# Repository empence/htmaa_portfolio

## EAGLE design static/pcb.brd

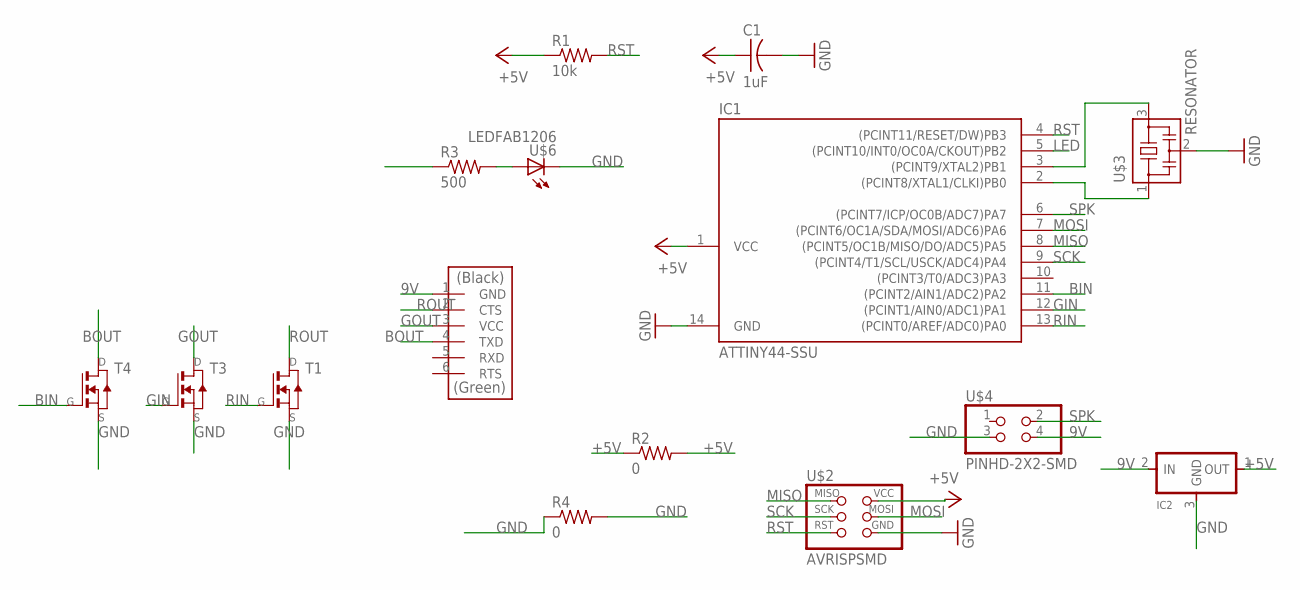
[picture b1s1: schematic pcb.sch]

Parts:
C1: 1uF; C1206FAB
IC1: ATTINY44-SSU; SOIC14
IC2: REGULATORSOT23; SOT23
R1: 10k; R1206FAB
R2, R4: 0; R1206FAB
R3: 500; R1206FAB
T1, T3, T4: NMOSFETSOT23; SOT-23
U$1: FTDI-SMD-HEADER; 1X06SMD
U$2: AVRISPSMD; 2X03SMD
U$3: RESONATOR; EFOBM
U$4: PINHD-2X2-SMD; 2X02SMD
U$6: LEDFAB1206; LED1206FAB

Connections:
9V: IC2.2 (IN), U$1.1 (GND), U$4.4
+5V: C1.1, IC1.1 (VCC), IC2.1 (OUT), R1.1, R2.1, R2.2, U$2.2 (VCC)
BIN: IC1.11 ((PCINT2/AIN1/ADC2)PA2), T4.3 (G)
BOUT: T4.1 (D), U$1.4 (TXD)
GIN: IC1.12 ((PCINT1/AIN0/ADC1)PA1), T3.3 (G)
GND: C1.2, IC1.14 (GND), IC2.3 (GND), R4.1, R4.2, T1.2 (S), T3.2 (S), T4.2 (S), U$2.6 (GND), U$3.2, U$4.3, U$6.2 (C)
GOUT: T3.1 (D), U$1.3 (VCC)
LED: IC1.5 ((PCINT10/INT0/OC0A/CKOUT)PB2), R3.1
MISO: IC1.8 ((PCINT5/OC1B/MISO/DO/ADC5)PA5), U$2.1 (MISO)
MOSI: IC1.7 ((PCINT6/OC1A/SDA/MOSI/ADC6)PA6), U$2.4 (MOSI)
unnamed: IC1.3 ((PCINT9/XTAL2)PB1), U$3.3
unnamed: IC1.2 ((PCINT8/XTAL1/CLKI)PB0), U$3.1
unnamed: R3.2, U$6.1 (A)
RIN: IC1.13 ((PCINT0/AREF/ADC0)PA0), T1.3 (G)
ROUT: T1.1 (D), U$1.2 (CTS)
RST: IC1.4 ((PCINT11/RESET/DW)PB3), R1.2, U$2.5 (RST)
SCK: IC1.9 ((PCINT4/T1/SCL/USCK/ADC4)PA4), U$2.3 (SCK)
SPK: IC1.6 ((PCINT7/ICP/OC0B/ADC7)PA7), U$4.2

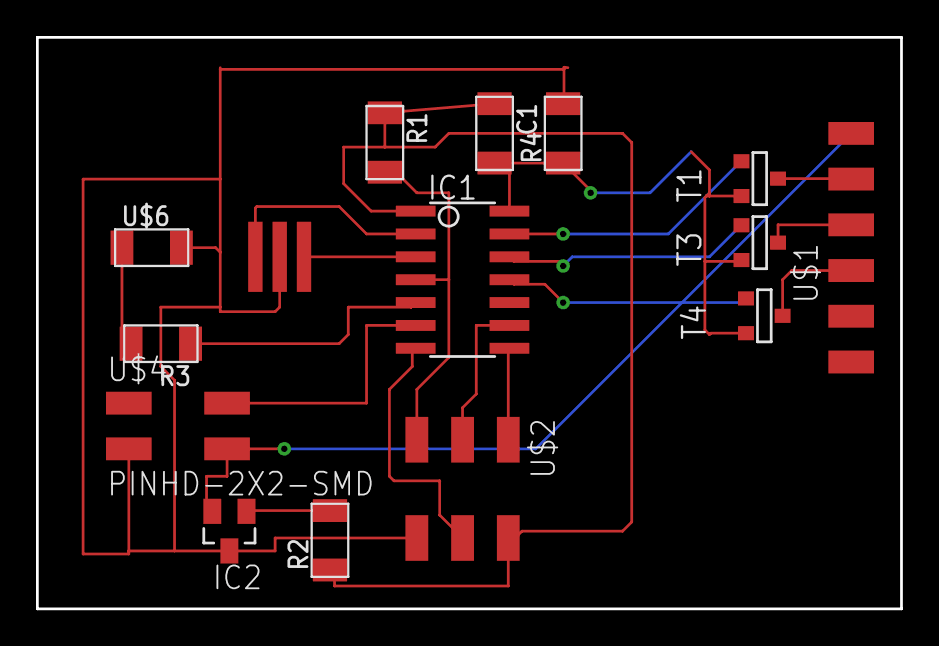
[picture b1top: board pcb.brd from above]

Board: 2 copper layers, 48.0 x 31.8 mm, 15 parts (0 on the bottom side), 18 nets.

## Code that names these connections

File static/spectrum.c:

// spectrum.c 
// communicate with a computer over serial (FTDI cable), to choose the color of an onboard RGB LED on pins 5, 6 and 7. 
// baud 115200 
// set lfuse to 0x5E for 20 MHz xtal
// based on code by Neil Gershenfeld 
//
// (c) Massachusetts Institute of Technology 2010
// This work may be reproduced, modified, distributed,
// performed, and displayed for any purpose. Copyright is
// retained and must be preserved. The work is provided
// as is; no warranty is provided, and users accept all 
// liability.
//

#include <avr/io.h>
#include <util/delay.h>
#include <avr/interrupt.h>
#include <avr/pgmspace.h>

#define output(directions,pin) (directions |= pin) // set port direction for output
#define set(port,pin) (port |= pin) // set port pin
#define clear(port,pin) (port &= (~pin)) // clear port pin
#define pin_test(pins,pin) (pins & pin) // test for port pin
#define bit_test(byte,bit) (byte & (1 << bit)) // test for bit set
#define bit_delay_time 8.5 // bit delay for 115200 with overhead
#define bit_delay() _delay_us(bit_delay_time) // RS232 bit delay
#define half_bit_delay() _delay_us(bit_delay_time/2) // RS232 half bit delay
#define char_delay() _delay_ms(10) // char delay

#define serial_port PORTA
#define serial_direction DDRA

#define serial_pins PINA
#define serial_pin_in (1 << PA0)
#define serial_pin_out (1 << PA1)
#define serial_interrupt (1 << PCIE0)
#define serial_interrupt_pin (1 << PCINT0)

#define red (1 << PA6)
#define green (1 << PB2)
#define blue (1 << PA7)

#define led_port_b PORTB
#define led_direction_b DDRB

void get_char(volatile unsigned char *pins, unsigned char pin, char *rxbyte, char wait) {
   //
   // read character into rxbyte on pins pin
   //    assumes line driver (inverts bits)
   //
   *rxbyte = 0;
   if (wait == 1){
   while (pin_test(*pins,pin))
      //
      // wait for start bit
      //
      ;
   }
   //
   // delay to middle of first data bit
   //
   half_bit_delay();
   bit_delay();
   //
   // unrolled loop to read data bits
   //
   if pin_test(*pins,pin)
      *rxbyte |= (1 << 0);
   else
      *rxbyte |= (0 << 0);
   bit_delay();
   if pin_test(*pins,pin)
      *rxbyte |= (1 << 1);
   else
      *rxbyte |= (0 << 1);
   bit_delay();
   if pin_test(*pins,pin)
      *rxbyte |= (1 << 2);
   else
      *rxbyte |= (0 << 2);
   bit_delay();
   if pin_test(*pins,pin)
      *rxbyte |= (1 << 3);
   else
      *rxbyte |= (0 << 3);
   bit_delay();
   if pin_test(*pins,pin)
      *rxbyte |= (1 << 4);
   else
      *rxbyte |= (0 << 4);
   bit_delay();
   if pin_test(*pins,pin)
      *rxbyte |= (1 << 5);
   else
      *rxbyte |= (0 << 5);
   bit_delay();
   if pin_test(*pins,pin)
      *rxbyte |= (1 << 6);
   else
      *rxbyte |= (0 << 6);
   bit_delay();
   if pin_test(*pins,pin)
      *rxbyte |= (1 << 7);
   else
      *rxbyte |= (0 << 7);
   //
   // wait for stop bit
   //
   bit_delay();
   half_bit_delay();
   }

 
// pin change interrupt handler
ISR(PCINT0_vect) {

   static char chr;
   get_char(&serial_pins, serial_pin_in, &chr, 1);
   if (chr == 'r'){
      clear(serial_port, red);
      set(serial_port, blue);
      set(led_port_b, green);
   }
   else if (chr == 'y'){
      clear(serial_port, red);
      set(serial_port, blue);
      clear(led_port_b, green);
   }
   else if (chr == 'g'){
      set(serial_port, red);
      set(serial_port, blue);
      clear(led_port_b, green);
   }
   else if (chr == 'c'){
      set(serial_port, red);
      clear(serial_port, blue);
      clear(led_port_b, green);
   }
   else if (chr == 'b'){
      set(serial_port, red);
      clear(serial_port, blue);
      set(led_port_b, green);
   }
   else if (chr == 'v'){
      clear(serial_port, red);
      clear(serial_port, blue);
      set(led_port_b, green);
   }
   else{  //do white
      clear(serial_port, red);
      clear(serial_port, blue);
      clear(led_port_b, green);
   }
   return;

   }

int main(void) {

   //
   // main
   //
   // set clock divider to /1
   //
   CLKPR = (1 << CLKPCE);
   CLKPR = (0 << CLKPS3) | (0 << CLKPS2) | (0 << CLKPS1) | (0 << CLKPS0);
   //
   // initialize serial output pins
   //
   set(serial_port, serial_pin_out);
   output(serial_direction, serial_pin_out);
   //initialize LED output pins
   set(serial_port, red);
   output(serial_direction, red);
   set(serial_port, blue);
   output(serial_direction, blue);
   set(led_port_b, green);
   output(led_direction_b, green);
   //
   // set up pin change interrupt on Rx pin (pin 13) and enable global interrupts
   //
   set(GIMSK, serial_interrupt);
   set (PCMSK0, serial_interrupt_pin);
   sei();
   
   //
   // main loop
   //
   while (1) {
      //do nothing in particular
      }
   }

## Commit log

2018-02-12 first commit: added all files from existing portfolio site
2018-04-17 final proj docs now have code, board schematics
2018-08-25 Change title, subtitle, and header color
